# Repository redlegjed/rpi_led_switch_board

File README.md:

# rpi_led_switch_board

Raspberry Pi LED and switch circuit board

This is a small board that can be fitted on top of the Raspberry Pi GPIO pins. It has the following features;

* 3 individual LEDs
* 1 RGB LED
* 2 slide switches
* 4 push buttons

All of these are separately routed to the Raspberry Pi's GPIO pins through a header so that they can be independently controlled.

Although the board was designed with the Raspberry Pi in mind, there's no reason why it couldn't be used with other similar boards by connecting wires to the relevant header pins.

The board was made as a simple example for learning to use the [Kicad](https://kicad-pcb.org/) circuit board design tools. The design was put together by following [this excellent example from Chris Gammell at Contextual electronics](https://www.youtube.com/watch?v=PlDOnSHkX2c). The Kicad design files are located in the *Rpi_led_switch_board* folder. This folder is a Kicad project so it should be able to be opened directly in Kicad.

The board was fabricated at [Osh Park](https://oshpark.com) and can be viewed [here](https://oshpark.com/shared_projects/ITYO5L7G). 

More details are given below:

# Circuit diagram

The circuit is very basic, it just connects all the components to the header pins. Specifically:

* All push buttons have one side connected to the header (R-Pi GPIO pin) and the other to Ground. 
* The slide switches have 3 pins, one is connected to Ground, one to 3.3V and middle (the slider) goes to the header where it's state can be detected.
* The individual LEDs have their anode (positive, long pin) side connected to the header (GPIO) and their cathode (short pin) to a 220 ohm resistor which goes to Ground.
* The RGB LED is set up as a common anode configuration. This means the positive side of the three LEDs inside it are all connected together and the negative sides come out on three pins. The positive side is connected to 3.3V and the negative sides go through 220 ohm resistors and then to the header (GPIO pins). In common anode configuration the GPIO pins must be set to LOW to turn on the LEDs and HIGH to turn them off. If using the *gpiozero* library *RGBLED* class to control them there is an extra argument needed to setup this. See below and *led_switch_board_demo.py* for examples.

# Components

All the components are available at [Adafruit](https://www.adafruit.com/) but can be found elsewhere as well.

* [Push buttons](https://www.adafruit.com/product/1009)
* [Slide switches](https://www.adafruit.com/product/805)
* [RGB LED 10mm diffused](https://www.adafruit.com/product/848)
* LEDs : any will do
* [220 ohm resistors](https://www.adafruit.com/product/2780)
* [Header](https://www.adafruit.com/product/2222) will need cutting

# Controlling using Python on a Raspberry Pi

The circuit board fits onto one end of the GPIO pin header, the end nearest the USB ports (see picture at the top of this page).

The easiest way to control the board is using the [*gpiozero* library](https://gpiozero.readthedocs.io/en/stable/). Set up all the components like this:

```python
from gpiozero import LED,RGBLED,Button

# Setup the hardware
# =======================

# Individual LEDs
led_red = LED(8)
led_green = LED(25)
led_blue = LED(24)

# Red, Green, Blue (RGB) LED
# Note: need to set the active_high argument to False
led_rgb = RGBLED(red=10,green=9,blue=11,active_high=False)

# Push buttons
button_red = Button(6)
button_green = Button(13)
button_blue = Button(26)
button_yellow = Button(19)

# Slide switches
switch_left = Button(20)
switch_right = Button(21)

```

From here you can use all the functions as described in the *gpiozero* Basic recipes.

```python

# Turn on LED
led_red.on()

# Turn off LED
led_blue.off()

# Set colour on RGB LED
led_rgb.color = (0, 1, 0)  # full green
led_rgb.color = (1, 0, 1)  # magenta
led_rgb.color = (1, 1, 0)  # yellow
led_rgb.color = (0, 1, 1)  # cyan
led_rgb.color = (1, 1, 1)  # white

# Check if button pressed
if button_red.is_pressed:
        print("Red Button is pressed")

# Same for switches
if switch_right.is_pressed:
        print("Right Switch is on")

```

A full example is given in *led_switch_board_demo.py*.

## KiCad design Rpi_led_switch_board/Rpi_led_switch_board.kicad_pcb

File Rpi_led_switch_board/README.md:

# Kicad design files

This folder is a Kicad project. It can be opened directly in Kicad using *File/Open Project*.

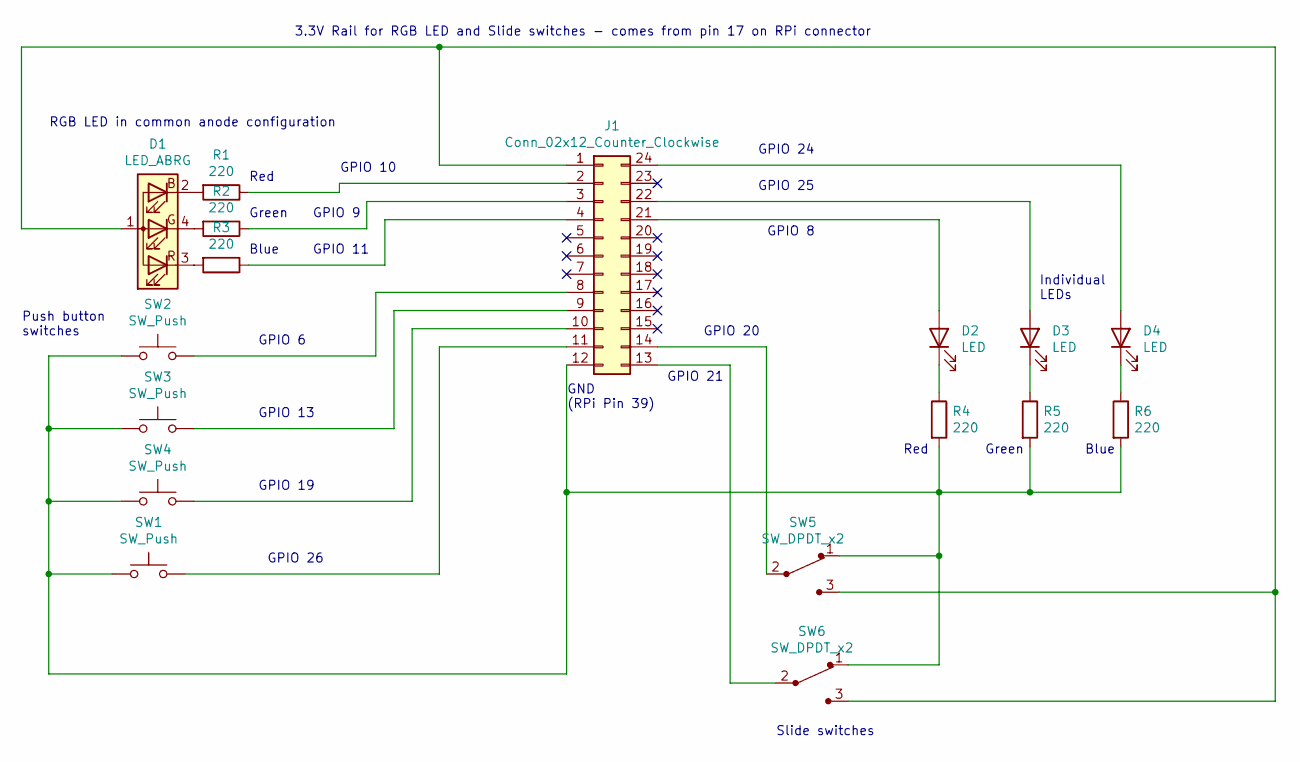
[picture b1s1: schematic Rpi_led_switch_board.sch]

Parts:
D1: LED_ABRG; LED_D5.0mm-4_RGB
D2, D3, D4: LED; LED_D5.0mm
J1: Conn_02x12_Counter_Clockwise; PinSocket_2x12_P2.54mm_Vertical
R1, R2, R3, R4, R5, R6: 220; R_Axial_DIN0207_L6.3mm_D2.5mm_P10.16mm_Horizontal
SW1, SW2, SW3, SW4: SW_Push; SW_PUSH-12mm
SW5, SW6: SW_DPDT_x2; Switch_Slide_11.6x4mm_EG1218

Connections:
unnamed: D1.1 (A), J1.1, SW5.3, SW6.3
unnamed: D1.2 (BK), R1.2
unnamed: D1.3 (RK), R3.2
unnamed: D1.4 (GK), R2.2
unnamed: D2.1 (K), R4.1
unnamed: D2.2 (A), J1.21
unnamed: D3.1 (K), R5.1
unnamed: D3.2 (A), J1.22
unnamed: D4.1 (K), R6.1
unnamed: D4.2 (A), J1.24
unnamed: J1.2, R1.1
unnamed: J1.3, R2.1
unnamed: J1.4, R3.1
unnamed: J1.8, SW2.2
unnamed: J1.9, SW3.2
unnamed: J1.10, SW4.2
unnamed: J1.11, SW1.2
unnamed: J1.12, R4.2, R5.2, R6.2, SW1.1, SW2.1, SW3.1, SW4.1, SW5.1, SW6.1
unnamed: J1.13, SW6.2
unnamed: J1.14, SW5.2

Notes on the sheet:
3.3V Rail for RGB LED and Slide switches - comes from pin 17 on RPi connector
RGB LED in common anode configuration
Push button switches
Slide switches
Individual LEDs
Red
Green
Blue
GND (RPi Pin 39)
GPIO 20
GPIO 21
GPIO 24
GPIO 25
GPIO 8
GPIO 10
GPIO 9
GPIO 11
GPIO 6
GPIO 13
GPIO 19
GPIO 26

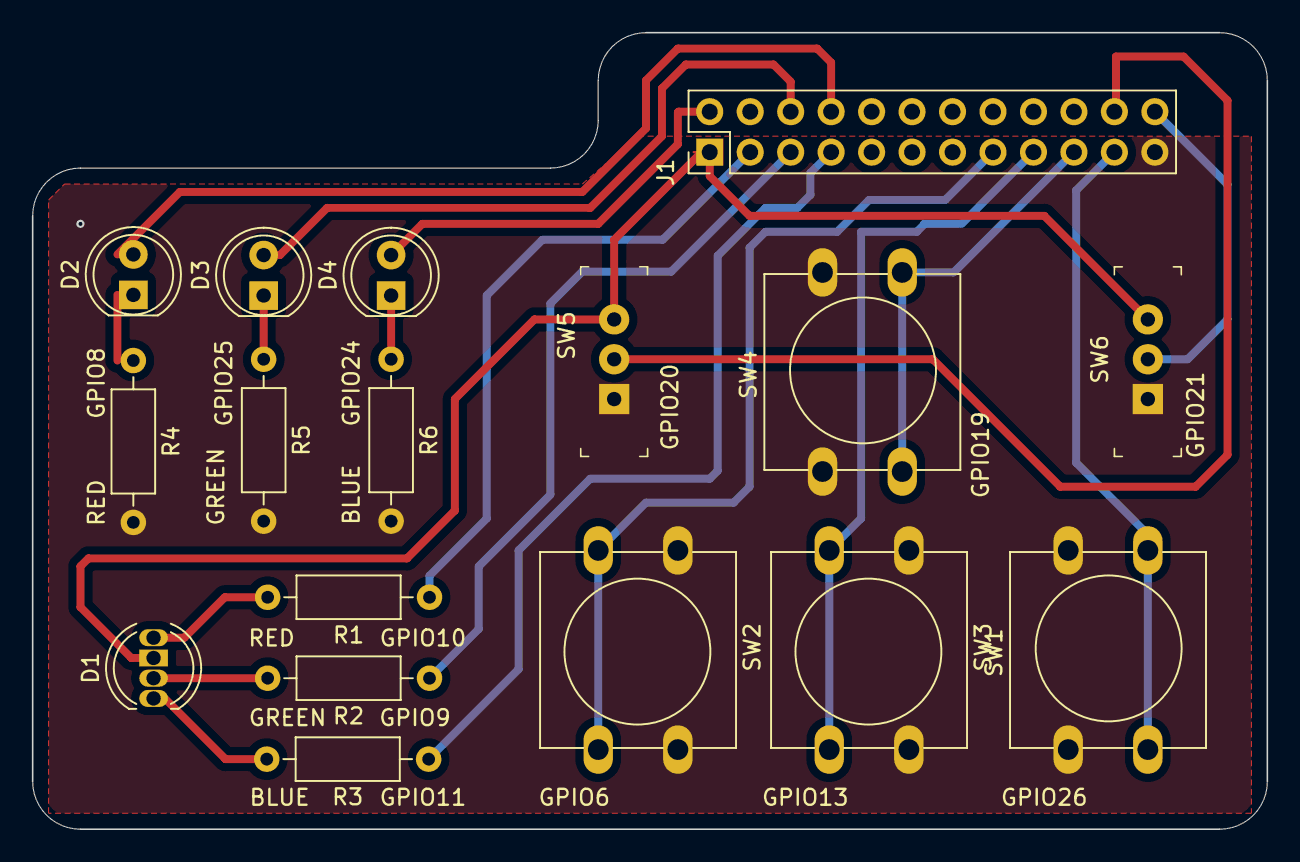
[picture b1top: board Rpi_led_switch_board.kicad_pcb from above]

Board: 2 copper layers, 77.5 x 50.0 mm, 17 parts (0 on the bottom side), 20 nets.

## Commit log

2020-09-14 Added content On branch master Changes to be committed: modified: README.md new file: Rpi_led_switch_board/Rpi_led_switch_board-cache.lib new file: Rpi_led_switch_board/Rpi_led_switch_board.kicad_pcb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
2020-09-14 Updated README files
2020-09-14 Updated README.md to mention the python demo.
2020-09-14 Added component list
    On branch master
    Changes to be committed:
    modified: README.md
